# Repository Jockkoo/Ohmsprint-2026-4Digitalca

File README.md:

# Smart Energy Meter — 4Digitalca
### OhmSPRINT 2026

An energy monitoring project developed by team **4Digitalca** for the OhmSPRINT 2026 hackathon.

The system combines an **ATM90E26 metering IC**, an **ESP32 microcontroller**, and a **Vue-based web application** for wireless data visualization via Bluetooth.

The project aims to measure RMS voltage and current, frequency, active power, and energy consumption.

## Repository Contents

- **project_files/** — KiCad schematics, PCB layout, component libraries, BOM, and manufacturing files.
- **firmware/** — ESP32 firmware written in C using ESP-IDF.
- **web/** — Web application for displaying data and configuring update intervals.

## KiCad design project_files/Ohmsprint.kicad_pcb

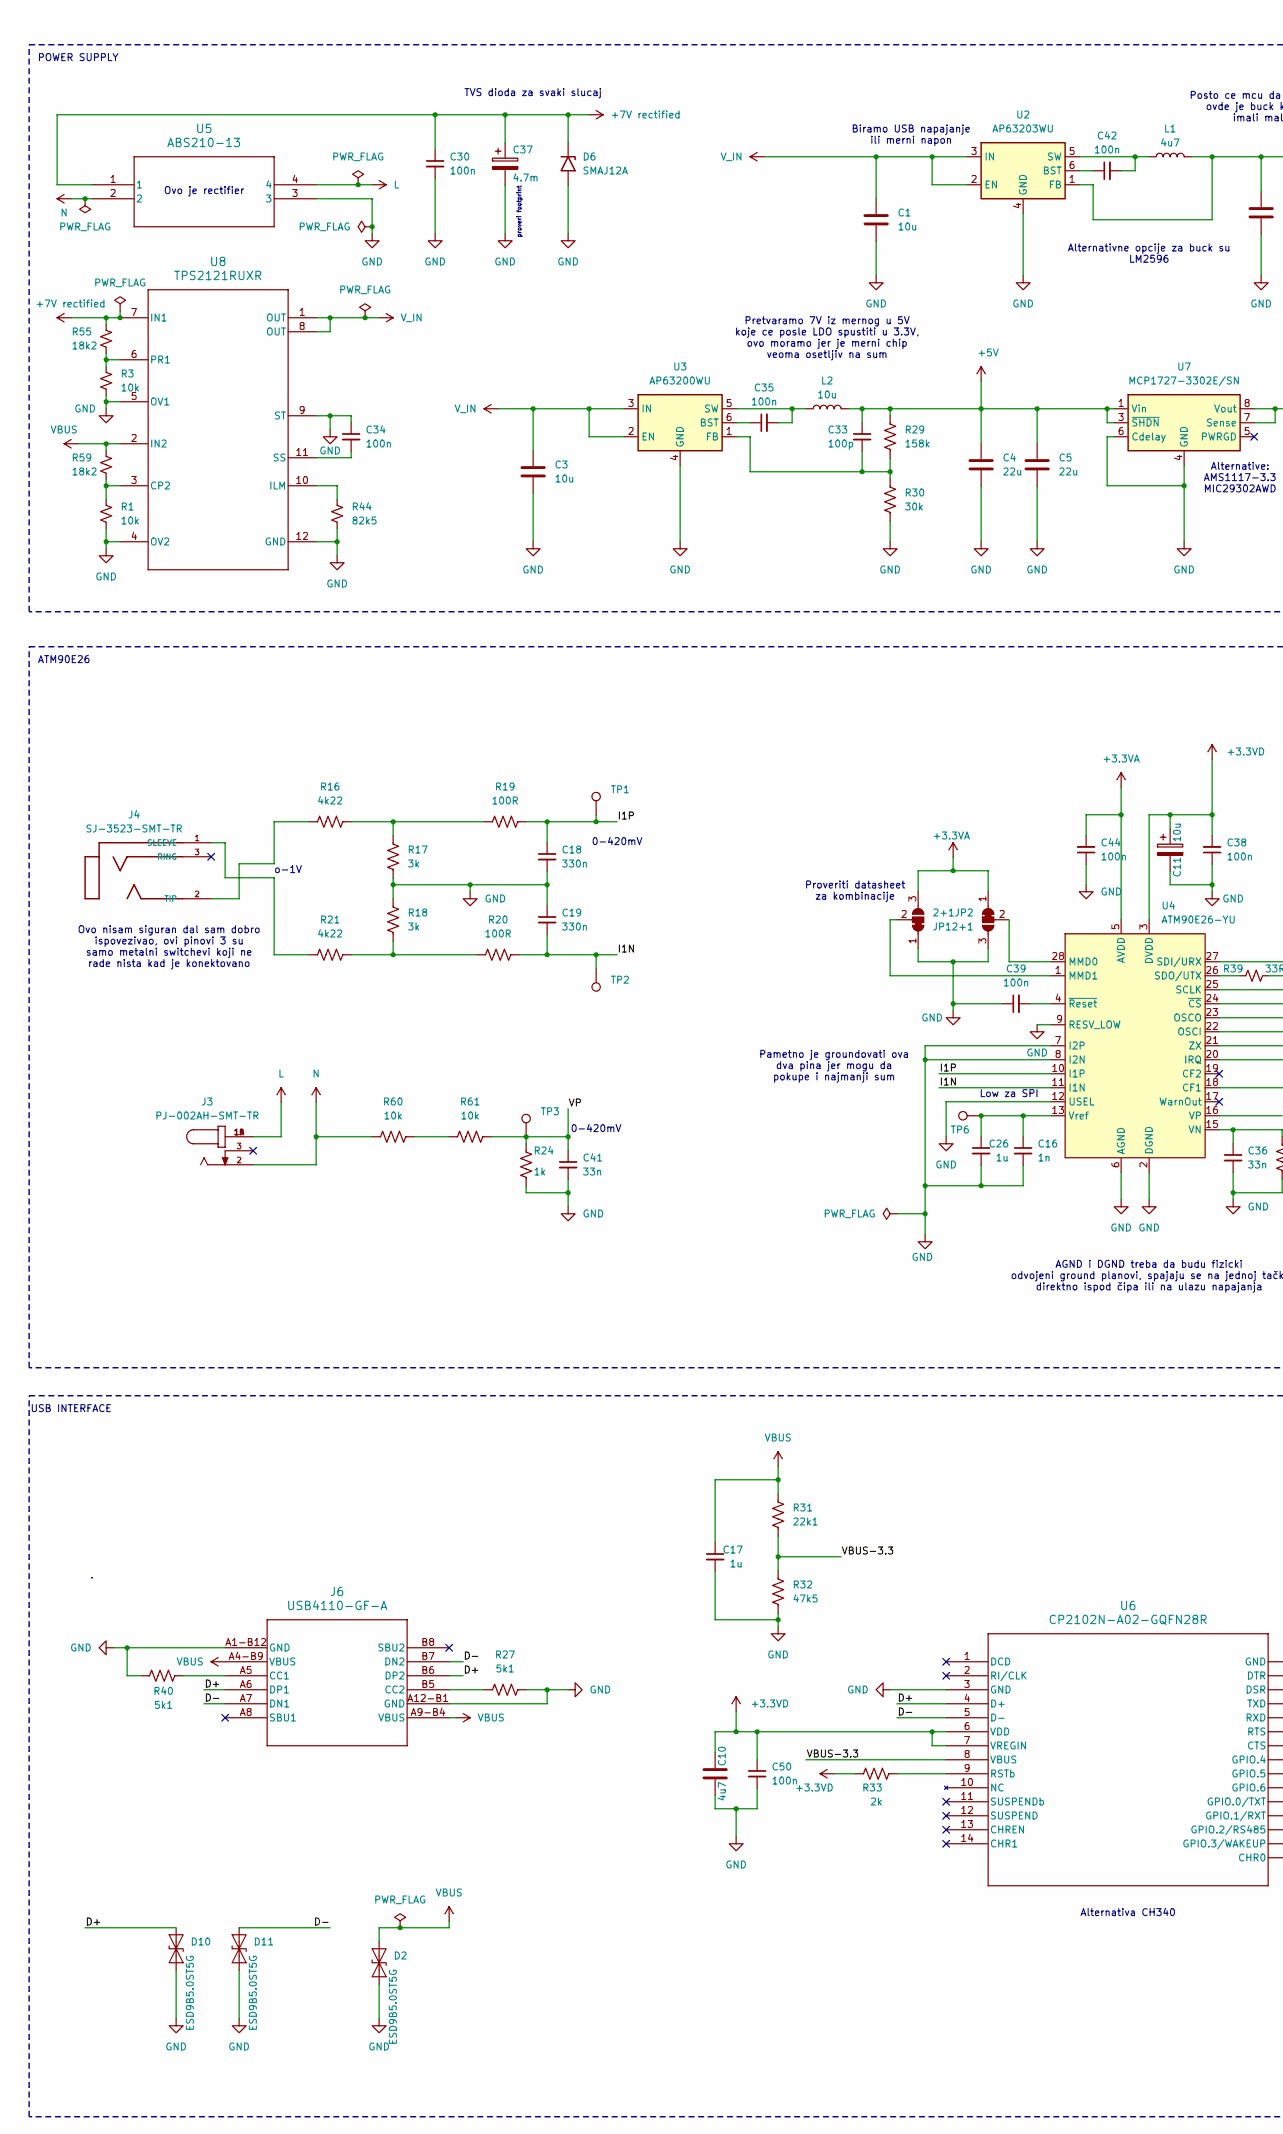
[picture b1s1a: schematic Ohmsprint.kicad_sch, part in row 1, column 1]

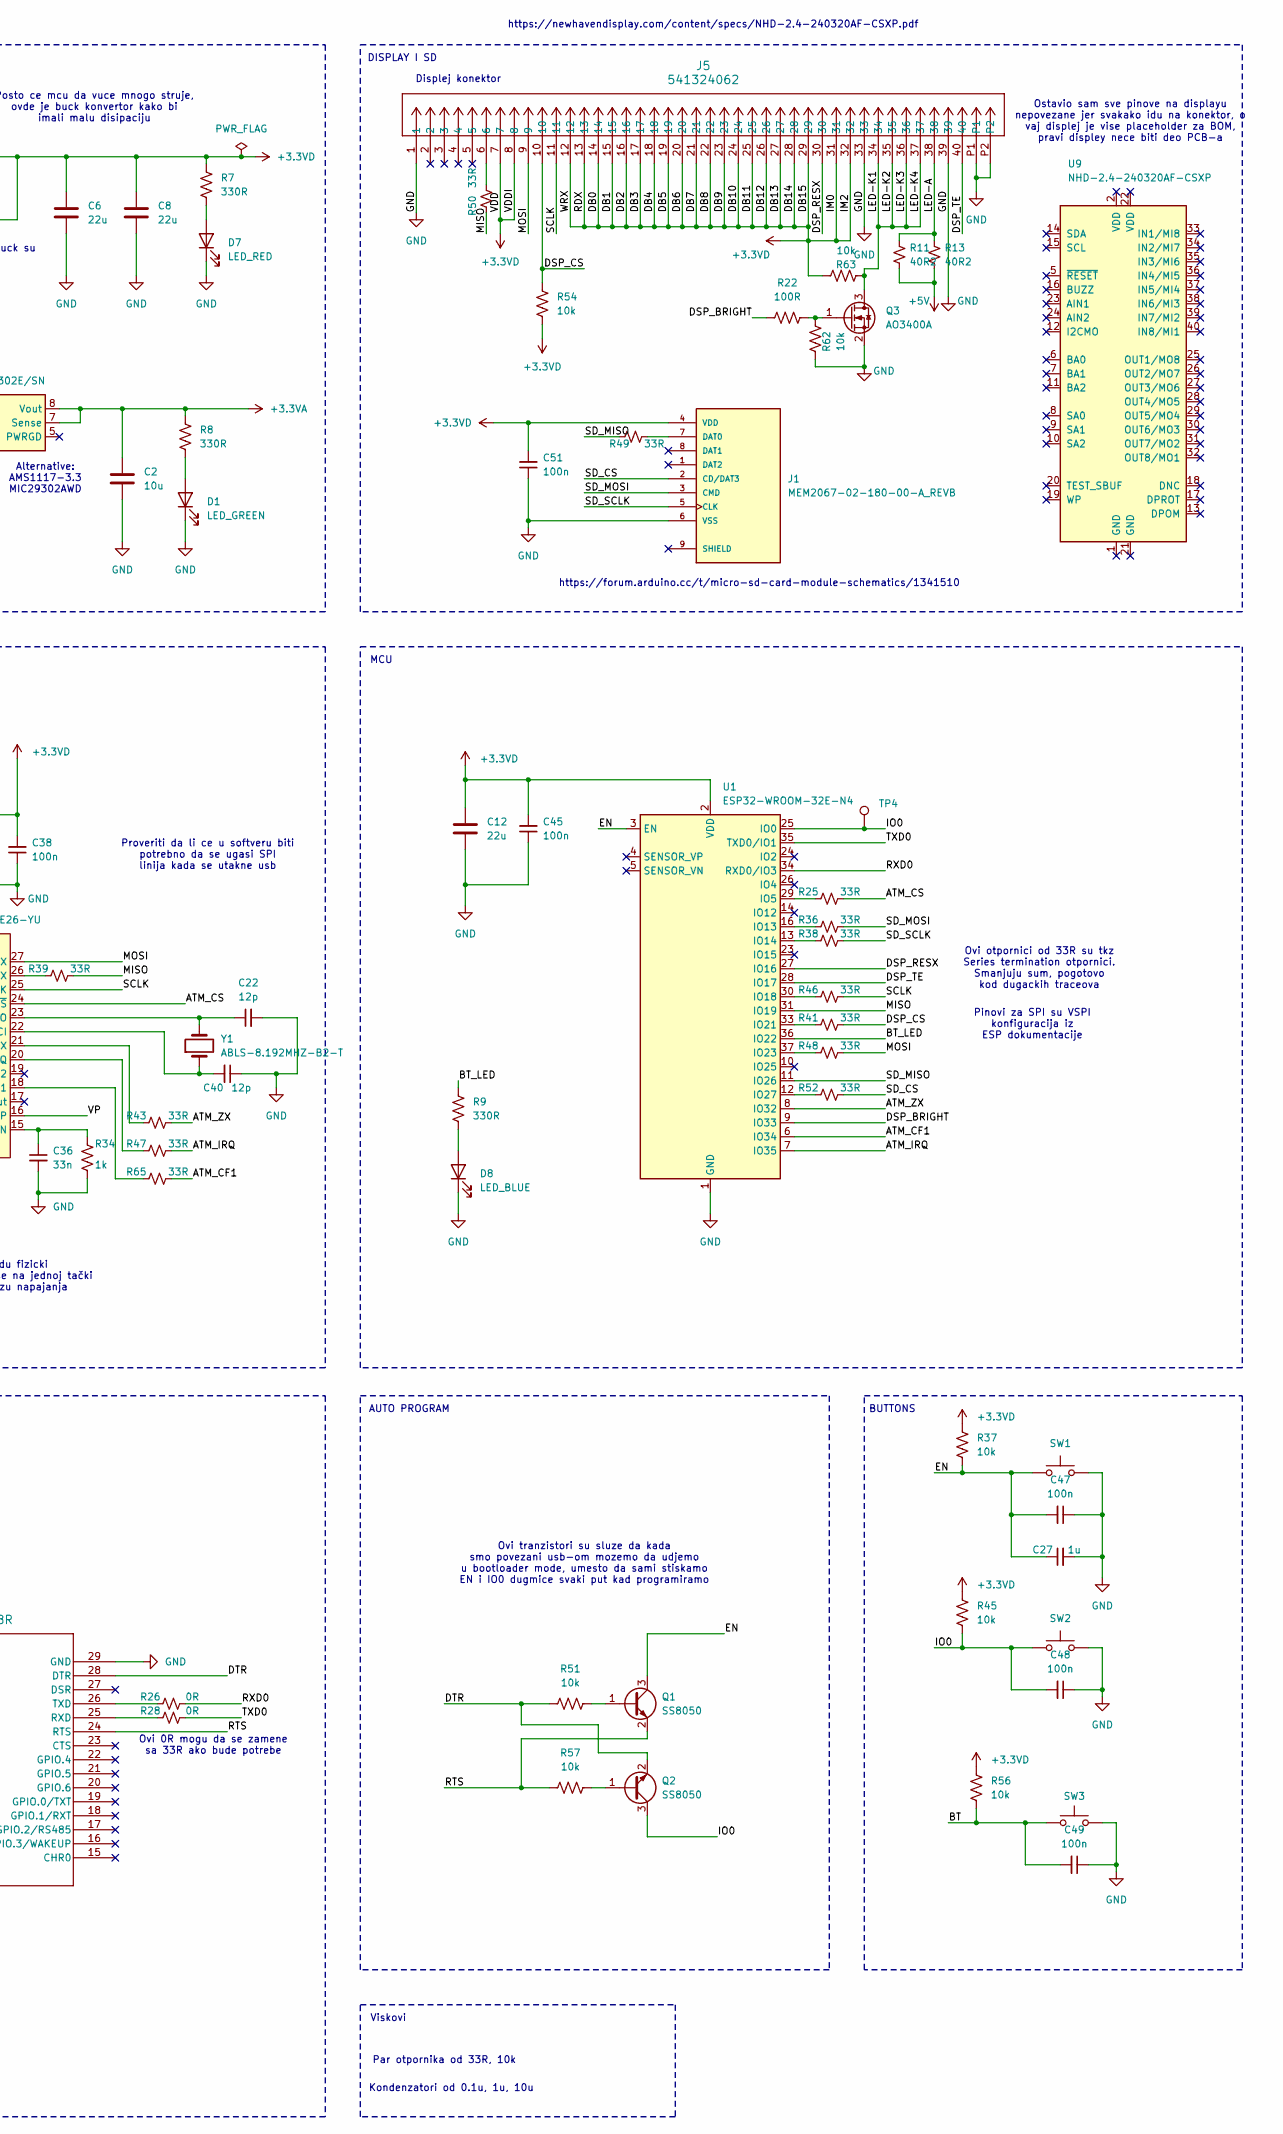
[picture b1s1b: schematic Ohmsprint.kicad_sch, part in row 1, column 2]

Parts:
C1, C2, C3: 10u; C_0805_2012Metric; MPN CL21B106KOQNNNE; DigiKey Part Number 1276-2872-1-ND
C4, C5, C6, C8, C12: 22u; C_1210_3225Metric; MPN CL32B226MOJNNNE; DigiKey Part Number 1276-3395-1-ND
C10: 4u7; C_0603_1608Metric; MPN GRM188R61E475KE11D; DigiKey Part Number 490-7203-1-ND
C11: 10u; CP_Elec_4x5.7; MPN EDH106M016A9BAA; DigiKey Part Number 399-17336-1-ND
C16: 1n; C_0603_1608Metric; MPN C0603C102K5RACTU; DigiKey Part Number 399-C0603C102K5RACTUCT-ND
C17, C26, C27: 1u; C_0603_1608Metric; MPN C0603C105K4RACTU; DigiKey Part Number 399-C0603C105K4RACTUCT-ND
C18, C19: 330n; C_0603_1608Metric; MPN C1608X7R1H334K080AC; DigiKey Part Number 445-5950-1-ND
C22, C40: 12p; C_0603_1608Metric; MPN KGQ15ACG2D120GT; DigiKey Part Number 478-KGQ15ACG2D120GTCT-ND
C30, C34, C35, C38, C39, C42, C44, C45, C47, C48, C49, C50, C51: 100n; C_0603_1608Metric; MPN C0603C104K3RACTU; DigiKey Part Number 399-C0603C104K3RACTUCT-ND
C33: 100p; C_0603_1608Metric; MPN GRM1885C1H101JA01D; DigiKey Part Number 490-1427-1-ND
C36, C41: 33n; C_0603_1608Metric; MPN C0603C333K4RACTU; DigiKey Part Number 399-C0603C333K4RACTUCT-ND
C37: 4.7m; CP_Elec_16x17.5; MPN EMHS160ARA472MLN0S; DigiKey Part Number 565-EMHS160ARA472MLN0SCT-ND
D1: LED_GREEN; LED_0805_2012Metric; MPN LTST-C171KGKT; DigiKey Part Number 160-1426-1-ND
D2, D10, D11: ESD9B5.0ST5G; D_SOD-923; MPN ESD9B5.0ST5G; DigiKey Part Number ESD9B5.0ST5GOSCT-ND
D6: SMAJ12A; D_SMA; MPN SMAJ12A; DigiKey Part Number SMAJ12ALFCT-ND
D7: LED_RED; LED_0805_2012Metric; MPN LTST-C171KRKT; DigiKey Part Number 160-1427-1-ND
D8: LED_BLUE; LED_0805_2012Metric; MPN LTST-C171TBKT; DigiKey Part Number 160-1645-1-ND
J1: MEM2067-02-180-00-A_REVB; GCT_MEM2067-02-180-00-A_REVB; MPN MEM2067-02-180-00-A
J3: PJ-002AH-SMT-TR; CUI_PJ-002AH-SMT-TR; MPN PJ-002AH-SMT-TR; DigiKey Part Number CP-002AHPJCT-ND
J4: SJ-3523-SMT-TR; CUI_SJ-3523-SMT-TR; MPN SJ-3523-SMT-TR; DigiKey Part Number CP-3523SJCT-ND
J5: 541324062; CON_541324062_MOL; MPN 0541324062; DigiKey Part Number WM3436CT-ND
J6: USB4110-GF-A; USB4110-GF-A_GCT; MPN USB4110-GF-A
JP1, JP2: 2+1; SolderJumper-3_P1.3mm_Bridged12_RoundedPad1.0x1.5mm
L1: 4u7; L_1210_3225Metric; MPN 1277AS-H-4R7M=P2; DigiKey Part Number 490-10594-1-ND
L2: 10u; L_1210_3225Metric; MPN AOTA-C322512Q100MT; DigiKey Part Number 535-AOTA-C322512Q100MTCT-ND
Q1, Q2: SS8050; SOT-23; MPN SS8050; DigiKey Part Number 5399-SS8050CT-ND
Q3: AO3400A; SOT-23; MPN AO3400A; DigiKey Part Number 4518-AO3400ACT-ND
R1, R3, R37, R45, R51, R54, R56, R57, R60, R61, R62, R63: 10k; R_0603_1608Metric; MPN RC0603FR-0710KL; DigiKey Part Number 311-10.0KHRCT-ND
R7, R8, R9: 330R; R_0603_1608Metric; MPN RC0603FR-07330RL; DigiKey Part Number 311-330HRCT-ND
R11, R13: 40R2; R_0805_2012Metric; MPN CRCW080540R2FKEA; DigiKey Part Number 541-40.2CCT-ND
R16, R21: 4k22; R_0603_1608Metric; MPN RC0603FR-074K22L; DigiKey Part Number 311-4.22KHRCT-ND
R17, R18: 3k; R_0603_1608Metric; MPN RC0603FR-073KL; DigiKey Part Number 311-3.00KHRCT-ND
R19, R20, R22: 100R; R_0603_1608Metric; MPN RC0603FR-07100RL; DigiKey Part Number 311-100HRCT-ND
R24, R34: 1k; R_0603_1608Metric; MPN RC0603FR-071KL; DigiKey Part Number 311-1.00KHRCT-ND
R25, R36, R38, R39, R41, R43, R46, R47, R48, R49, R50, R52, R65: 33R; R_0603_1608Metric; MPN RC0603FR-0733RL; DigiKey Part Number 13-RC0603FR-0733RLCT-ND
R26, R28: 0R; R_0603_1608Metric; MPN RC0603JR-070RL; DigiKey Part Number 311-0.0GRCT-ND
R27, R40: 5k1; R_0603_1608Metric; MPN RC0603FR-075K1L; DigiKey Part Number 311-5.10KHRCT-ND
R29: 158k; R_0603_1608Metric; MPN RC0603FR-07158KL; DigiKey Part Number 311-158KHRCT-ND
R30: 30k; R_0603_1608Metric; MPN RC0603FR-0730KL; DigiKey Part Number 311-30.0KHRCT-ND
R31: 22k1; R_0603_1608Metric; MPN RC0603FR-0722K1L; DigiKey Part Number 311-22.1KHRCT-ND
R32: 47k5; R_0603_1608Metric; MPN RC0603FR-1047K5L; DigiKey Part Number 13-RC0603FR-1047K5LCT-ND
R33: 2k; R_0603_1608Metric; MPN RC0603FR-072KL; DigiKey Part Number 311-2.00KHRCT-ND
R44: 82k5; R_0805_2012Metric; MPN RMCF0805FT82K5; DigiKey Part Number RMCF0805FT82K5CT-ND
R55, R59: 18k2; R_0603_1608Metric; MPN RC0603FR-0718K2L; DigiKey Part Number 311-18.2KHRCT-ND
SW1, SW2: SW_Push_1_Red; SWITCH_45SK43SMTR92LFS; MPN PTS645SK43SMTR92 LFS; DigiKey Part Number CKN9084CT-ND
SW3: SW_Push_2_Blue; SWITCH_43SMTR92LFS; MPN PTS645SM43SMTR92 LFS; DigiKey Part Number CKN9112CT-ND
TP1, TP2, TP3, TP4, TP6: TestPoint; TestPoint_Pad_D2.0mm
U1: ESP32-WROOM-32E-N4; ESP32-WROOM-32D; MPN ESP32-WROOM-32E-N4; DigiKey Part Number 1965-ESP32-WROOM-32E-N4CT-ND
U2: AP63203WU; TSOT-23-6; MPN AP63203WU-7; DigiKey Part Number AP63203WU-7DICT-ND
U3: AP63200WU; TSOT-23-6; MPN AP63200WU-7; DigiKey Part Number AP63200WU-7DICT-ND
U4: ATM90E26-YU; SSOP-28_5.3x10.2mm_P0.65mm; MPN ATM90E26-YU-R; DigiKey Part Number ATM90E26-YU-RCT-ND
U5: ABS210-13; SON_S210-13_DIO; MPN ABS210-13; DigiKey Part Number ABS210-13DICT-ND
U6: CP2102N-A02-GQFN28R; QFN28_5X5_SIL; MPN CP2102N-A02-GQFN28R; DigiKey Part Number 336-5890-1-ND
U7: MCP1727-3302E/SN; SOIC-8_3.9x4.9mm_P1.27mm; MPN MCP1727T-3302E/SN; DigiKey Part Number MCP1727T-3302E/SNCT-ND
U8: TPS2121RUXR; RUX0012A; MPN TPS2121RUXR; DigiKey Part Number 296-53410-1-ND
U9: NHD-2.4-240320AF-CSXP; EA_eDIPTFT32-XXX; MPN NHD-2.4-240320AF-CSXP; DigiKey Part Number 757-NHD-2.4-240320AF-CSXP-ND
Y1: ABLS-8.192MHZ-B2-T; Crystal_SMD_HC49-SD; MPN ABLS-8.192MHZ-B2-T; DigiKey Part Number 535-9090-1-ND

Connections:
+3.3VA: C2.1, C44.2, JP1.3 (B), JP2.1 (A), R8.1, U4.5 (AVDD), U7.7 (Sense), U7.8 (Vout)
+3.3VD: C6.1, C8.1, C10.1, C11.1, C12.1, C38.2, C45.2, C50.1, C51.2, J1.4 (VDD), J5.7, J5.8, J5.12, J5.13, J5.14, J5.15, J5.16, J5.17, J5.18, J5.19, J5.20, J5.21, J5.22, J5.23, J5.24, J5.25, J5.26, J5.27, J5.28, J5.29, J5.31, J5.32, L1.2, R7.1, R33.1, R37.2, R45.2, R54.1, R56.2, R63.1, U1.2 (VDD), U2.1 (FB), U4.3 (DVDD), U6.6 (VDD), U6.7 (VREGIN); also elsewhere on the board
+5V: C4.1, C5.1, C33.1, L2.2, R11.2, R13.2, R29.1, U7.1 (Vin), U7.2 (Vin), U7.3 (~SHDN)
+7V rectified: C30.1, C37.1, D6.1 (A1), R55.1, U5.1, U8.7 (IN1)
/ATM_CF1: R65.2, U1.6 (IO34)
/ATM_CS: R25.2, U4.24 (~CS)
/ATM_IRQ: R47.2, U1.7 (IO35)
/ATM_ZX: R43.2, U1.8 (IO32)
/BT: C49.2, R56.1, SW3.1
/BT_LED: R9.1, U1.36 (IO22)
/D+: D10.2 (A2), J6.A6 (DP1), J6.B6 (DP2), U6.4 (D+)
/D-: D11.2 (A2), J6.A7 (DN1), J6.B7 (DN2), U6.5 (D-)
/DSP_BRIGHT: R22.1, U1.9 (IO33)
/DSP_CS: J5.10, R41.2, R54.2
/DSP_RESX: J5.30, U1.27 (IO16)
/DSP_TE: J5.40, U1.28 (IO17)
/DTR: Q2.2 (E), R51.2, U6.28 (DTR)
/EN: C27.1, C47.2, Q1.3 (C), R37.1, SW1.1, U1.3 (EN)
/I1N: C19.2, R20.2, TP2.1 (1_1), U4.11 (I1N)
/I1P: C18.1, R19.2, TP1.1 (1_1), U4.10 (I1P)
/IO0: C48.2, Q2.3 (C), R45.1, SW2.1, TP4.1 (1_1), U1.25 (IO0)
/LED-A: J5.38, R11.1, R13.1
/LED-K1: J5.34, J5.35, J5.36, J5.37, Q3.3 (D), R63.2
/MISO: R39.2, R50.1, U1.31 (IO19)
/MOSI: J5.9, R48.2, U4.27 (SDI/URX)
/RTS: Q1.2 (E), R57.2, U6.24 (RTS)
/RXD0: R26.2, U1.34 (RXD0/IO3)
/SCLK: J5.11, R46.2, U4.25 (SCLK)
/SD_CS: J1.2 (CD/DAT3), R52.2; also elsewhere on the board
/SD_MISO: R49.1, U1.11 (IO26)
/SD_MOSI: J1.3 (CMD), R36.2
/SD_SCLK: J1.5 (CLK), R38.2
/TXD0: R28.2, U1.35 (TXD0/IO1)
/VBUS-3.3: R31.2, R32.1, U6.8 (VBUS)
/VP: C41.1, R24.2, R61.1, TP3.1 (1_1), U4.16 (VP)
GND: C1.2, C2.2, C3.2, C4.2, C5.2, C6.2, C8.2, C10.2, C11.2, C12.2, C16.2, C17.2, C18.2, C19.1, C22.2, C26.2, C27.2, C30.2, C34.1, C36.2, C37.2, C38.1, C39.1, C40.1, C41.2, C44.1, C45.1, C47.1, C48.1, C49.1, C50.2, C51.1, D1.1 (K), D2.1 (A1), D6.2 (A2), D7.1 (K), D8.1 (K), D10.1 (A1), D11.1 (A1), J1.6 (VSS), J5.1, J5.33, J5.39, J5.P1, J5.P2, J6.A1-B12 (GND), J6.A12-B1 (GND), JP1.1 (A), JP2.3 (B), Q3.2 (S), R1.2, R3.2, R17.2, R18.1, R24.1, R27.2, R30.2, R32.2, R34.1, R40.1, R44.2, R62.2, SW1.2, SW2.2, SW3.2, U1.1 (GND), U1.15 (GND), U1.38 (GND), U1.39 (GND), U2.4 (GND), U3.4 (GND), U4. (RESV_LOW), U4.2 (DGND), U4.6 (AGND), U4.7 (I2P), U4.8 (I2N), U4.9 (DGND), U4.12 (USEL), U4.14 (AGND), U5.3, U6.3 (GND), U6.29 (GND), U7.4 (GND), U7.6 (Cdelay), U8.4 (OV2), U8.5 (OV1), U8.9 (ST), U8.12 (GND)
L: J3.1A, J3.1B, U5.4
N: J3.2, R60.2, U5.2
unnamed: D1.2 (A), R8.2
unnamed: D7.2 (A), R7.2
unnamed: D8.2 (A), R9.2
unnamed: J1.7 (DAT0), R49.2
unnamed: J4.1 (SLEEVE), R21.1
unnamed: J4.2 (TIP), R16.1
unnamed: J5.6, R50.2
unnamed: J6.A5 (CC1), R40.2
unnamed: J6.B5 (CC2), R27.1
unnamed: JP1.2 (C), U4.1 (MMD1)
unnamed: JP2.2 (C), U4.28 (MMD0)
unnamed: Q1.1 (B), R51.1
unnamed: Q2.1 (B), R57.1
unnamed: Q3.1 (G), R22.2, R62.1
unnamed: R16.2, R17.1, R19.1
unnamed: R18.2, R20.1, R21.2
unnamed: R60.1, R61.2
unnamed: R25.1, U1.29 (IO5)
unnamed: R36.1, U1.16 (IO13)
unnamed: R38.1, U1.13 (IO14)
unnamed: R46.1, U1.30 (IO18)
unnamed: R41.1, U1.33 (IO21)
unnamed: R48.1, U1.37 (IO23)
unnamed: R52.1, U1.12 (IO27)
unnamed: C42.1, U2.6 (BST)
unnamed: C42.2, L1.1, U2.5 (SW)
unnamed: C35.1, U3.6 (BST)
unnamed: C33.2, R29.2, R30.1, U3.1 (FB)
unnamed: C35.2, L2.1, U3.5 (SW)
unnamed: R65.1, U4.18 (CF1)
unnamed: R47.1, U4.20 (IRQ)
unnamed: C40.2, U4.22 (OSCI), Y1.1
unnamed: C22.1, U4.23 (OSCO), Y1.2
unnamed: R39.1, U4.26 (SDO/UTX)
unnamed: C36.1, R34.2, U4.15 (VN)
unnamed: C16.1, C26.1, TP6.1 (1_1), U4.13 (Vref)
unnamed: R43.1, U4.21 (ZX)
unnamed: C39.2, U4.4 (~Reset)
unnamed: R33.2, U6.9 (RSTb)
unnamed: R28.1, U6.25 (RXD)
unnamed: R26.1, U6.26 (TXD)
unnamed: R1.1, R59.2, U8.3 (CP2)
unnamed: R44.1, U8.10 (ILM)
unnamed: R3.1, R55.2, U8.6 (PR1)
unnamed: C34.2, U8.11 (SS)
VBUS: C17.1, D2.2 (A2), J6.A4-B9 (VBUS), J6.A9-B4 (VBUS), R31.1, R59.1, U8.2 (IN2)
V_IN: C1.1, C3.1, U2.2 (EN), U2.3 (IN), U3.2 (EN), U3.3 (IN), U8.1 (OUT), U8.8 (OUT)

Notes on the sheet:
o-1V
TVS dioda za svaki slucaj
0-420mV
AUTO PROGRAM
BUTTONS
Par otpornika od 33R, 10k
MCU
Alternative: AMS1117-3.3 MIC29302AWD
https://forum.arduino.cc/t/micro-sd-card-module-schematics/1341510
POWER SUPPLY
Ostavio sam sve pinove na displayu nepovezane jer svakako idu na konektor, o vaj displej je vise placeholder za BOM, pravi displey nece biti deo PCB-a
Biramo USB napajanje ili merni napon
Kondenzatori od 0.1u, 1u, 10u
Posto ce mcu da vuce mnogo struje, ovde je buck konvertor kako bi imali malu disipaciju
Alternativa CH340
Proveriti da li ce u softveru biti potrebno da se ugasi SPI linija kada se utakne usb
Ovi otpornici od 33R su tkz Series termination otpornici. Smanjuju sum, pogotovo kod dugackih traceova
https://newhavendisplay.com/content/specs/NHD-2.4-240320AF-CSXP.pdf
Displej konektor
Pinovi za SPI su VSPI konfiguracija iz ESP dokumentacije
proveri footprint
Alternativne opcije za buck su LM2596
Ovi 0R mogu da se zamene sa 33R ako bude potrebe
Pametno je groundovati ova dva pina jer mogu da pokupe i najmanji sum
Ovo je rectifier
Pretvaramo 7V iz mernog u 5V koje ce posle LDO spustiti u 3.3V, ovo moramo jer je merni chip veoma osetljiv na sum
AGND i DGND treba da budu fizicki odvojeni ground planovi, spajaju se na jednoj tački direktno ispod čipa ili na ulazu napajanja
Ovo nisam siguran dal sam dobro ispovezivao, ovi pinovi 3 su samo metalni switchevi koji ne rade nista kad je konektovano
Viskovi
Low za SPI
Proveriti datasheet za kombinacije
DISPLAY I SD
USB INTERFACE
Ovi tranzistori su sluze da kada smo povezani usb-om mozemo da udjemo u bootloader mode, umesto da sami stiskamo EN i IO0 dugmice svaki put kad programiramo
ATM90E26

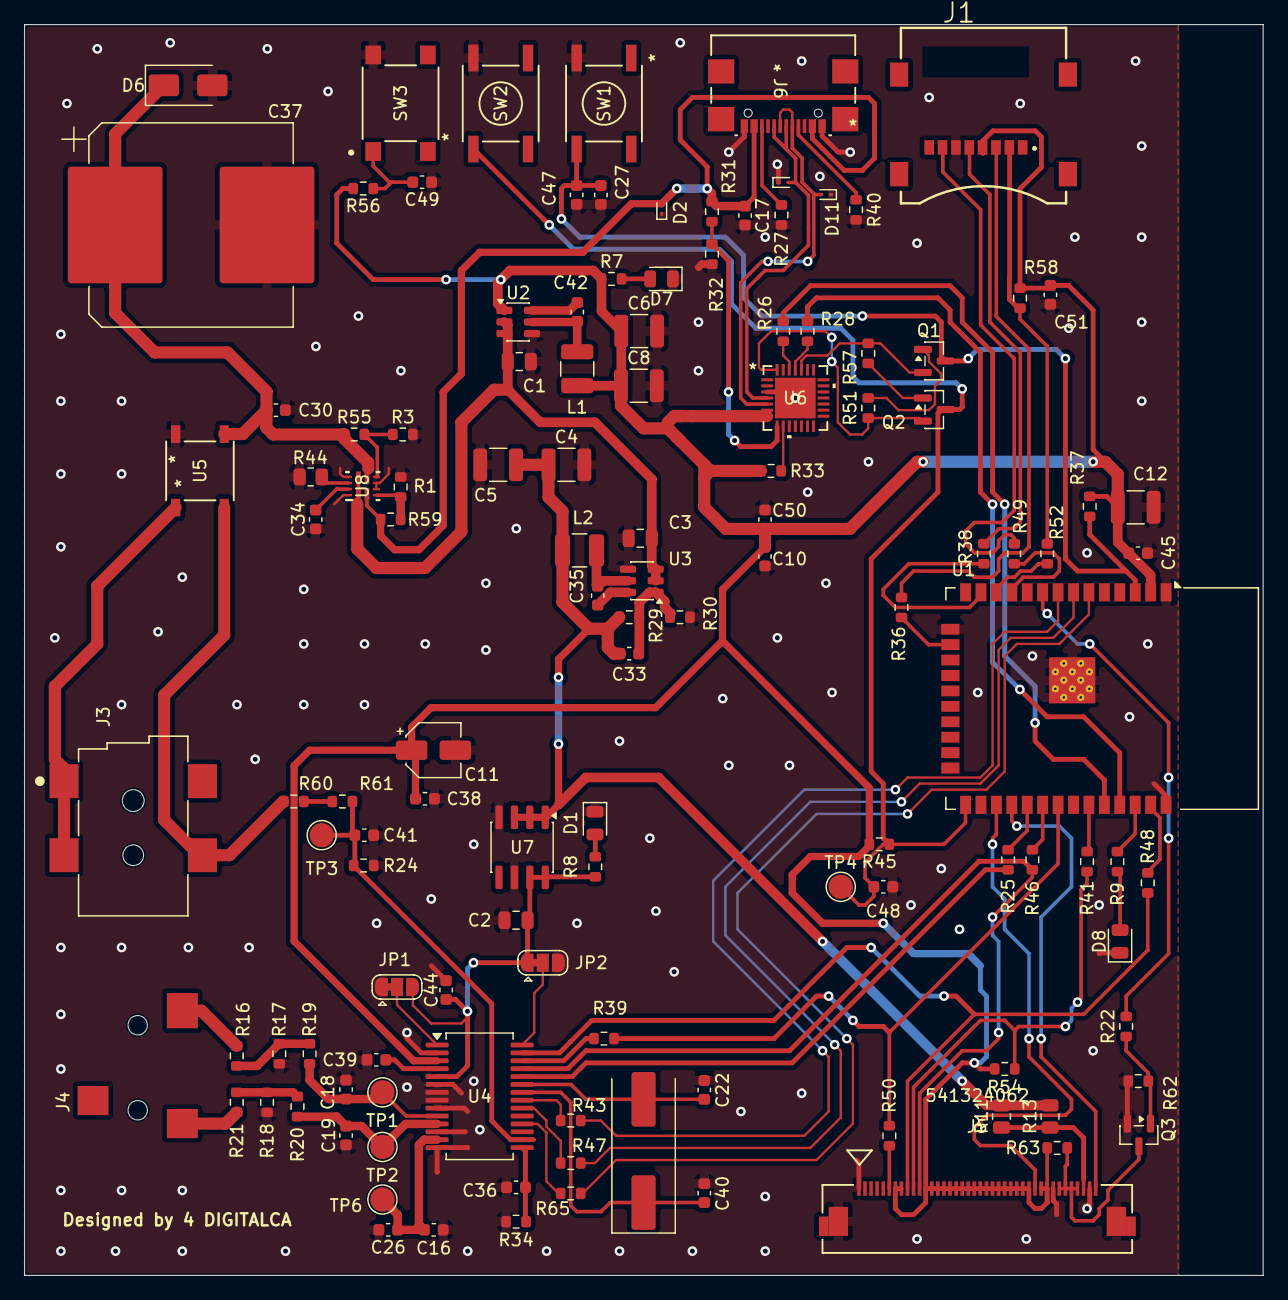
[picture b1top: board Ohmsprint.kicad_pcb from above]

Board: 2 copper layers, 102.0 x 103.0 mm, 123 parts (0 on the bottom side), 85 nets.

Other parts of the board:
R58: 10k; R_0603_1608Metric

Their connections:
+3.3VD: R58.2; also elsewhere on the board
/SD_CS: R58.1; also elsewhere on the board

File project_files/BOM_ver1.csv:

"Reference","Qty","Value","MPN","MNF"
"C1,C2,C3","4","10u","CL21B106KOQNNNE","Samsung Electro-Mechanics"
"C4,C5,C6,C8,C12","5","22u","CL32B226MOJNNNE","Samsung Electro-Mechanics"
"C10","1","4u7","GRM188R61E475KE11D","Murata Electronics"
"C11","1","10u","EDH106M016A9BAA","KEMET"
"C16","1","1n","C0603C102K5RACTU","KEMET"
"C17,C26,C27","3","1u","C0603C105K4RACTU","KEMET"
"C18,C19","2","330n","C1608X7R1H334K080AC","TDK"
"C22,C40","2","12p","KGQ15ACG2D120GT","KYOCERA AVX"
"C30,C34,C35,C38,C39,C42,C44,C45,C47,C48,C49,C50,C51","15","100n","C0603C104K3RACTU","KEMET"
"C33","1","100p","GRM1885C1H101JA01D","Murata Electronics"
"C36,C41","2","33n","C0603C333K4RACTU","KEMET"
"C37","1","4.7m","EMHS160ARA472MLN0S","Chemi-Con"
"D1","1","LED_GREEN","LTST-C171KGKT","Lite-On Inc."
"D2,D10,D11","3","ESD9B5.0ST5G","ESD9B5.0ST5G","onsemi"
"D5","1","BAT760","BAT760","Shenzhen Slkormicro Semicon Co., Ltd."
"D6","1","SMAJ12A","SMAJ12A","Littelfuse Inc."
"D7","1","LED_RED","LTST-C171KRKT","Lite-On Inc."
"D8","1","LED_BLUE","LTST-C171TBKT","Lite-On Inc."
"D9","1","LED_ORANGE","LTST-C170KFKT","Lite-On Inc."
"J2","1","MEM2067-02-180-00-A","MEM2067-02-180-00-A","  GCT"
"J3","1","PJ-002AH-SMT-TR","PJ-002AH-SMT-TR","Same Sky (Formerly CUI Devices)"
"J4","1","SJ-3523-SMT-TR","SJ-3523-SMT-TR","Same Sky (Formerly CUI Devices)"
"J5","1","541324062","0541324062","Molex"
"J6","1","USB4110-GF-A","USB4110-GF-A","GCT"
"L1","1","4u7","1277AS-H-4R7M=P2","Murata Electronics"
"L2","1","10u","AOTA-C322512Q100MT","Abracon LLC"
"Q1,Q2","2","SS8050","SS8050","Shenzhen Slkormicro Semicon Co., Ltd."
"Q3","1","AO3400A","AO3400A","UMW"
"R1,R3,R37,R45,R51,R53,R54,R56,R57,R58,R60,R61,R62,R63,R64","17","10k","RC0603FR-0710KL","YAGEO"
"R6,R15","2","10R","CRCW080510R0JNEA","Vishay Dale"
"R7,R8,R9,R10","4","330R","RC0603FR-07330RL","YAGEO"
"R11,R13","2","40R2","CRCW080540R2FKEA","Vishay Dale"
"R12","1","56k","RC0603FR-0756KL","YAGEO"
"R14,R23","2","20R","CRCW080520R0JNEA","Vishay Dale"
"R16,R21","2","4k22","RC0603FR-074K22L","YAGEO"
"R17,R18","2","3k","RC0603FR-073KL","YAGEO"
"R19,R20,R22","3","100R","RC0603FR-07100RL","YAGEO"
"R24,R34","3","1k","RC0603FR-071KL","YAGEO"
"R25,R36,R38,R39,R41,R46,R48,R49,R50,R52","14","33R","RC0603FR-0733RL","YAGEO"
"R26,R28,R35","3","0R","RC0603JR-070RL","YAGEO"
"R27,R40","2","5k1","RC0603FR-075K1L","YAGEO"
"R29","1","158k","RC0603FR-07158KL","YAGEO"
"R30","1","30k","RC0603FR-0730KL","YAGEO"
"R31,R42","2","22k1","RC0603FR-0722K1L","YAGEO"
"R32","1","47k5","RC0603FR-1047K5L","YAGEO"
"R33","1","2k","RC0603FR-072KL","YAGEO"
"R44","1","82k5","RMCF0805FT82K5","Stackpole Electronics Inc"
"R55,R59","2","18k2","RC0603FR-0718K2L","YAGEO"
"SW1,SW2","2","SW_Push_1_Red","PTS645SK43SMTR92 LFS","C&K"
"SW3","1","SW_Push_2_Blue","PTS645SM43SMTR92 LFS","C&K"
"U1","1","ESP32-WROOM-32E-N4","ESP32-WROOM-32E-N4","Espressif Systems"
"U2","1","AP63203WU","AP63203WU-7","Diodes Incorporated"
"U3","1","AP63200WU","AP63200WU-7","Diodes Incorporated"
"U4","1","ATM90E26-YU","ATM90E26-YU-R","Microchip Technology"
"U5","1","ABS210-13","ABS210-13","Diodes Incorporated"
"U6","1","CP2102N-A02-GQFN28R","CP2102N-A02-GQFN28R","Silicon Labs"
"U7","1","MCP1727-3302E/SN","MCP1727T-3302E/SN","Microchip Technology"
"U8","1","TPS2121RUXR","TPS2121RUXR","Texas Instruments"
"U9","1","NHD-2.4-240320AF-CSXP","NHD-2.4-240320AF-CSXP","Newhaven Display Intl"
"Y1","1","ABLS-8.192MHZ-B2-T","ABLS-8.192MHZ-B2-T","Abracon LLC"

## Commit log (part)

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2026-04-07 Dodati connectori i rectifier
2026-04-07 Slika seme
2026-04-08 Buck konvertor, jumperi, SPI, DigiKey proizvodi
2026-04-09 Novi power supply, doradjena sema
2026-04-09 basic web project structure
2026-04-09 ble works, also some wifi code added, not tested
2026-04-09 ble firmware and web ui humble beginnings
2026-04-10 formatting
2026-04-11 Displej, SD kartica, DigiKey modeli
2026-04-12 Power MUX, Display, Part numbers, Manufacturers and Footprints
2026-04-12 Displej napajanje reseno (valjda)
2026-04-12 Generisan Bill of Materials
2026-04-13 Update PCB layout-a
2026-04-15 USB :)
2026-04-15 Uradjeno pola rutiranja
2026-04-16 Uradjen PCB
2026-04-16 Generisani Gerber i Drill
2026-04-18 firm: refactored the ble into a nice api
2026-04-18 soft: ble api and new web ui
